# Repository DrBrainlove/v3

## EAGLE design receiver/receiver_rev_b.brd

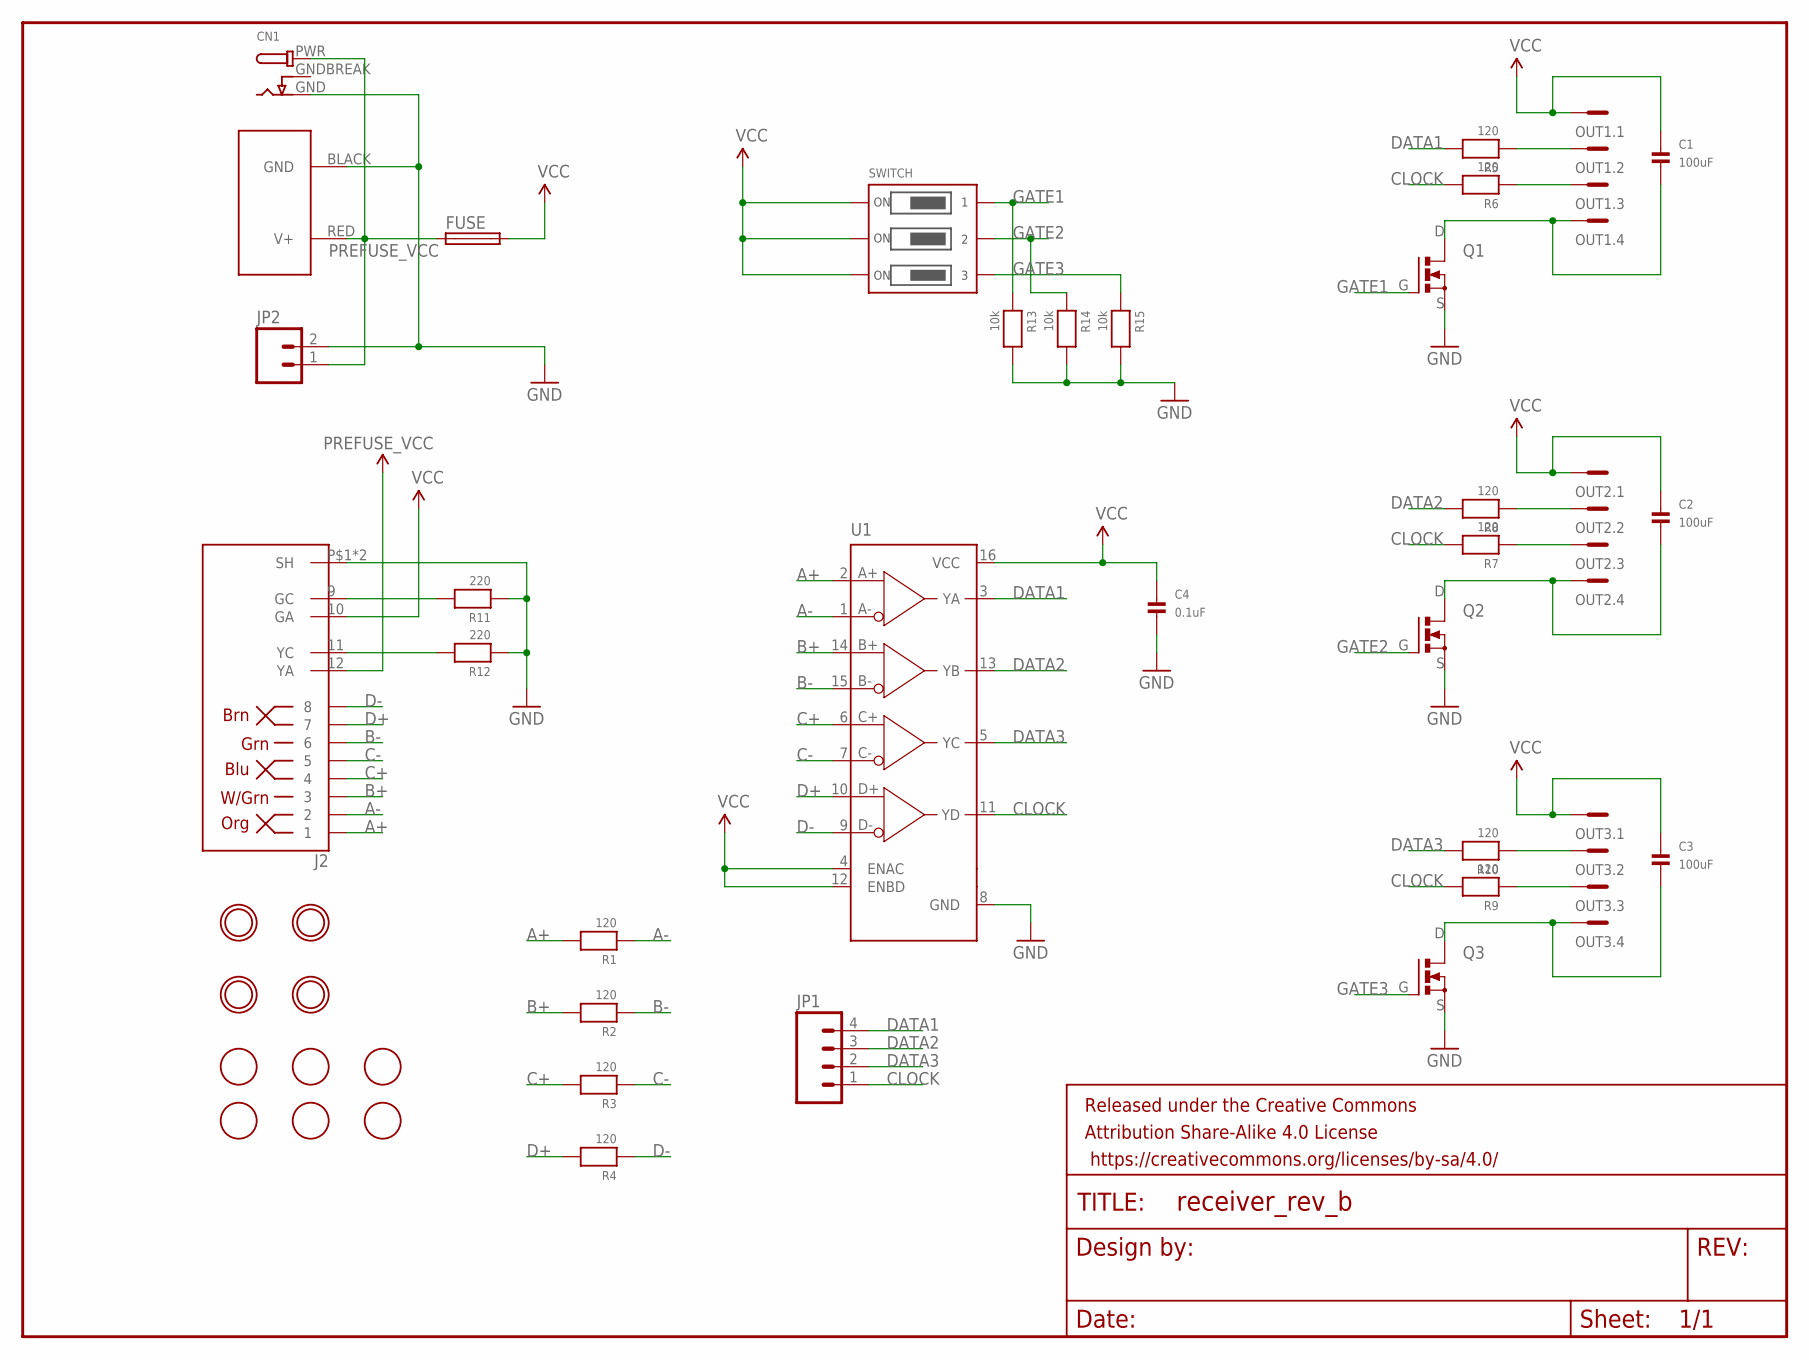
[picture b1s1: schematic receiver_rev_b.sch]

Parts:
C1, C2, C3: 100uF; 1206
C4: 0.1uF; 0603-MINI
CN1: DCBARRELPTH; DCJACK_2MM_PTH
FID1, FID2, FID3, FID4, FID5, FID6: FIDUCIAL; FIDUCIAL_1MM
FRAME1: FRAME-LETTERNO_PACKAGE; DUMMY
FUSE: MINI-FUSE-HOLDER3557; FUSE-HOLDER-3557
J1: POWERPOLE_POWER45A_HORIZONTAL_DRILL; POWERPOLE_PAIR_45A_HORIZ_HOLE
J2: RJHSE-5381; RJHSE-538X
JP1: M04PTH; 1X04
JP2: M02PTH4; 1X02_XTRA_BIG
OUT1, OUT2, OUT3: MC4
Q1, Q2, Q3: DMN1019USN; SC59
R1, R2, R3, R4, R5, R6, R7, R8, R9, R10: 120; 0603-MINI
R11, R12: 220; 0603-MINI
R13, R14, R15: 10k; 0603-MINI
SWITCH: DIP-SWITCH-3PIN194; 194-DIP-SWITCH
U1: MAX3093/94UE; TSSOP16
U$3, U$4, U$5, U$6: MOUNTINGHOLE3.0THIN; MOUNTINGHOLE_3.0_PLATEDTHIN

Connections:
A+: J2.1, R1.2, U1.2 (A+)
A-: J2.2, R1.1, U1.1 (A-)
B+: J2.3, R2.2, U1.14 (B+)
B-: J2.6, R2.1, U1.15 (B-)
C+: J2.4, R3.2, U1.6 (C+)
C-: J2.5, R3.1, U1.7 (C-)
CLOCK: JP1.1, R6.2, R7.2, R9.2, U1.11 (YD)
D+: J2.7, R4.2, U1.10 (D+)
D-: J2.8, R4.1, U1.9 (D-)
DATA1: JP1.4, R5.2, U1.3 (YA)
DATA2: JP1.3, R8.2, U1.13 (YB)
DATA3: JP1.2, R10.2, U1.5 (YC)
GATE1: Q1.G, R13.1, SWITCH.1B
GATE2: Q2.G, R14.1, SWITCH.2B
GATE3: Q3.G, R15.1, SWITCH.3B
GND: C4.2, CN1.GND, J1.BLACK (GND), J2.P$1 (SH), J2.P$2 (SH), JP2.2, Q1.S, Q2.S, Q3.S, R11.1, R12.1, R13.2, R14.2, R15.2, U1.8 (GND)
GNDBREAK: CN1.GNDBREAK
unnamed: OUT1.2, R5.1
unnamed: OUT1.3, R6.1
unnamed: C1.2, OUT1.4, Q1.D
unnamed: OUT2.2, R8.1
unnamed: OUT2.3, R7.1
unnamed: C2.2, OUT2.4, Q2.D
unnamed: OUT3.2, R10.1
unnamed: OUT3.3, R9.1
unnamed: C3.2, OUT3.4, Q3.D
unnamed: J2.9 (GC), R11.2
unnamed: J2.11 (YC), R12.2
PREFUSE_VCC: CN1.PWR, FUSE.A1 (1), FUSE.A2 (1), J1.RED (V+), J2.12 (YA), JP2.1
VCC: C1.1, C2.1, C3.1, C4.1, FUSE.B1 (2), FUSE.B2 (2), J2.10 (GA), OUT1.1, OUT2.1, OUT3.1, SWITCH.1A, SWITCH.2A, SWITCH.3A, U1.4 (ENAC), U1.12 (ENBD), U1.16 (VCC)

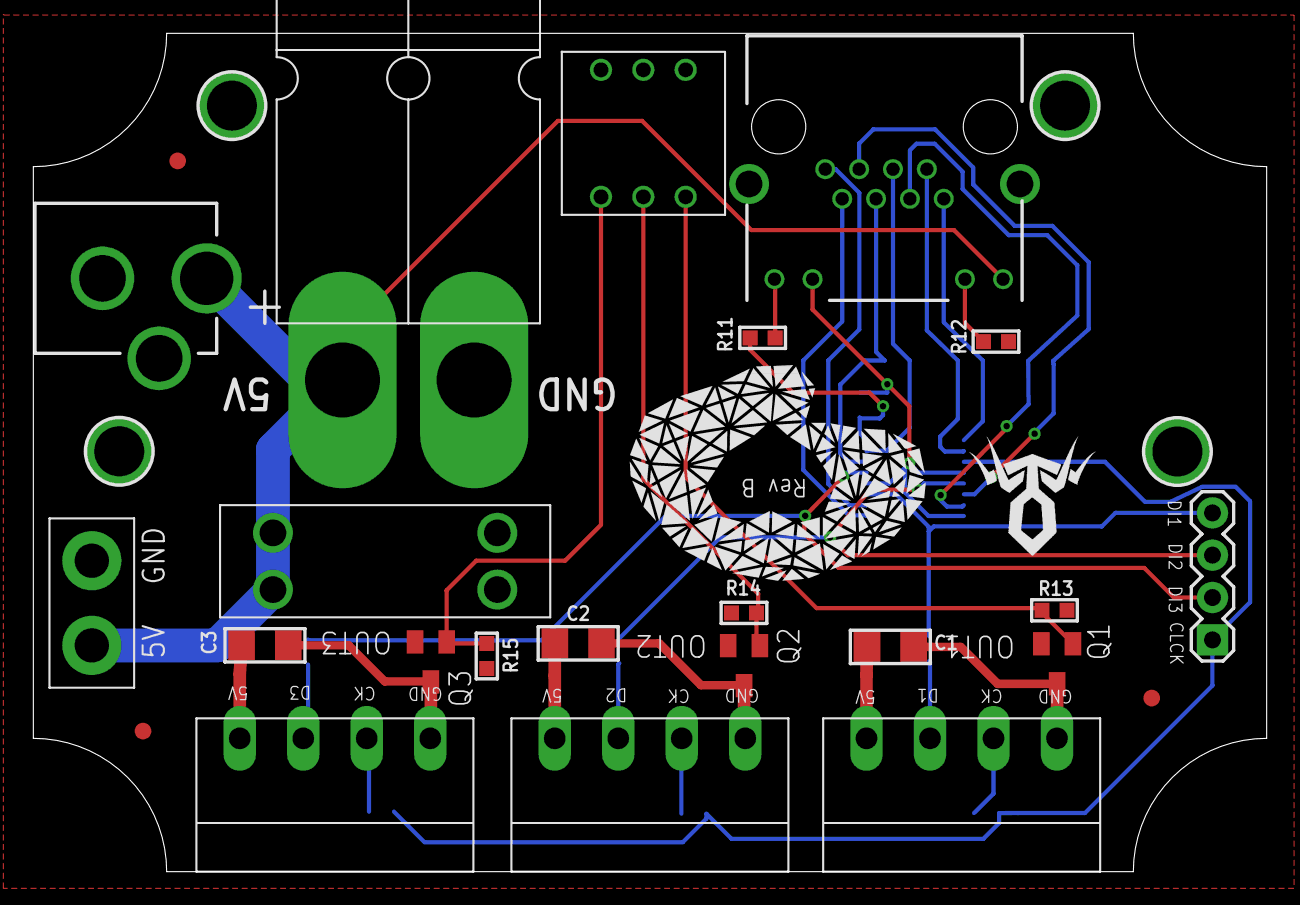
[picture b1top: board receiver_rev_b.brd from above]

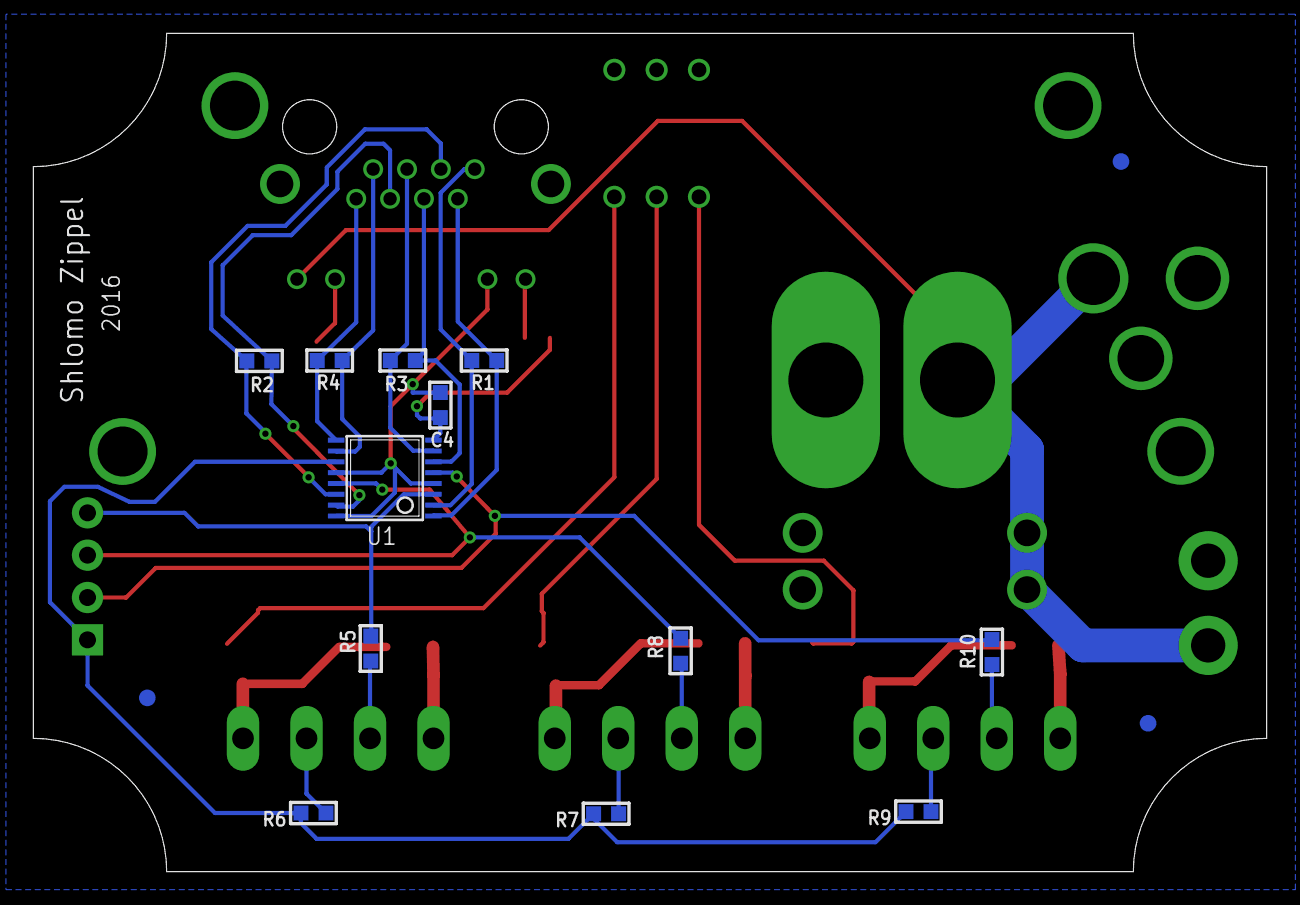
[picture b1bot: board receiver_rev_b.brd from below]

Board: 2 copper layers, 74.0 x 50.3 mm, 45 parts (15 on the bottom side), 29 nets.

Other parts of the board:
U$2: AK-B-FT21

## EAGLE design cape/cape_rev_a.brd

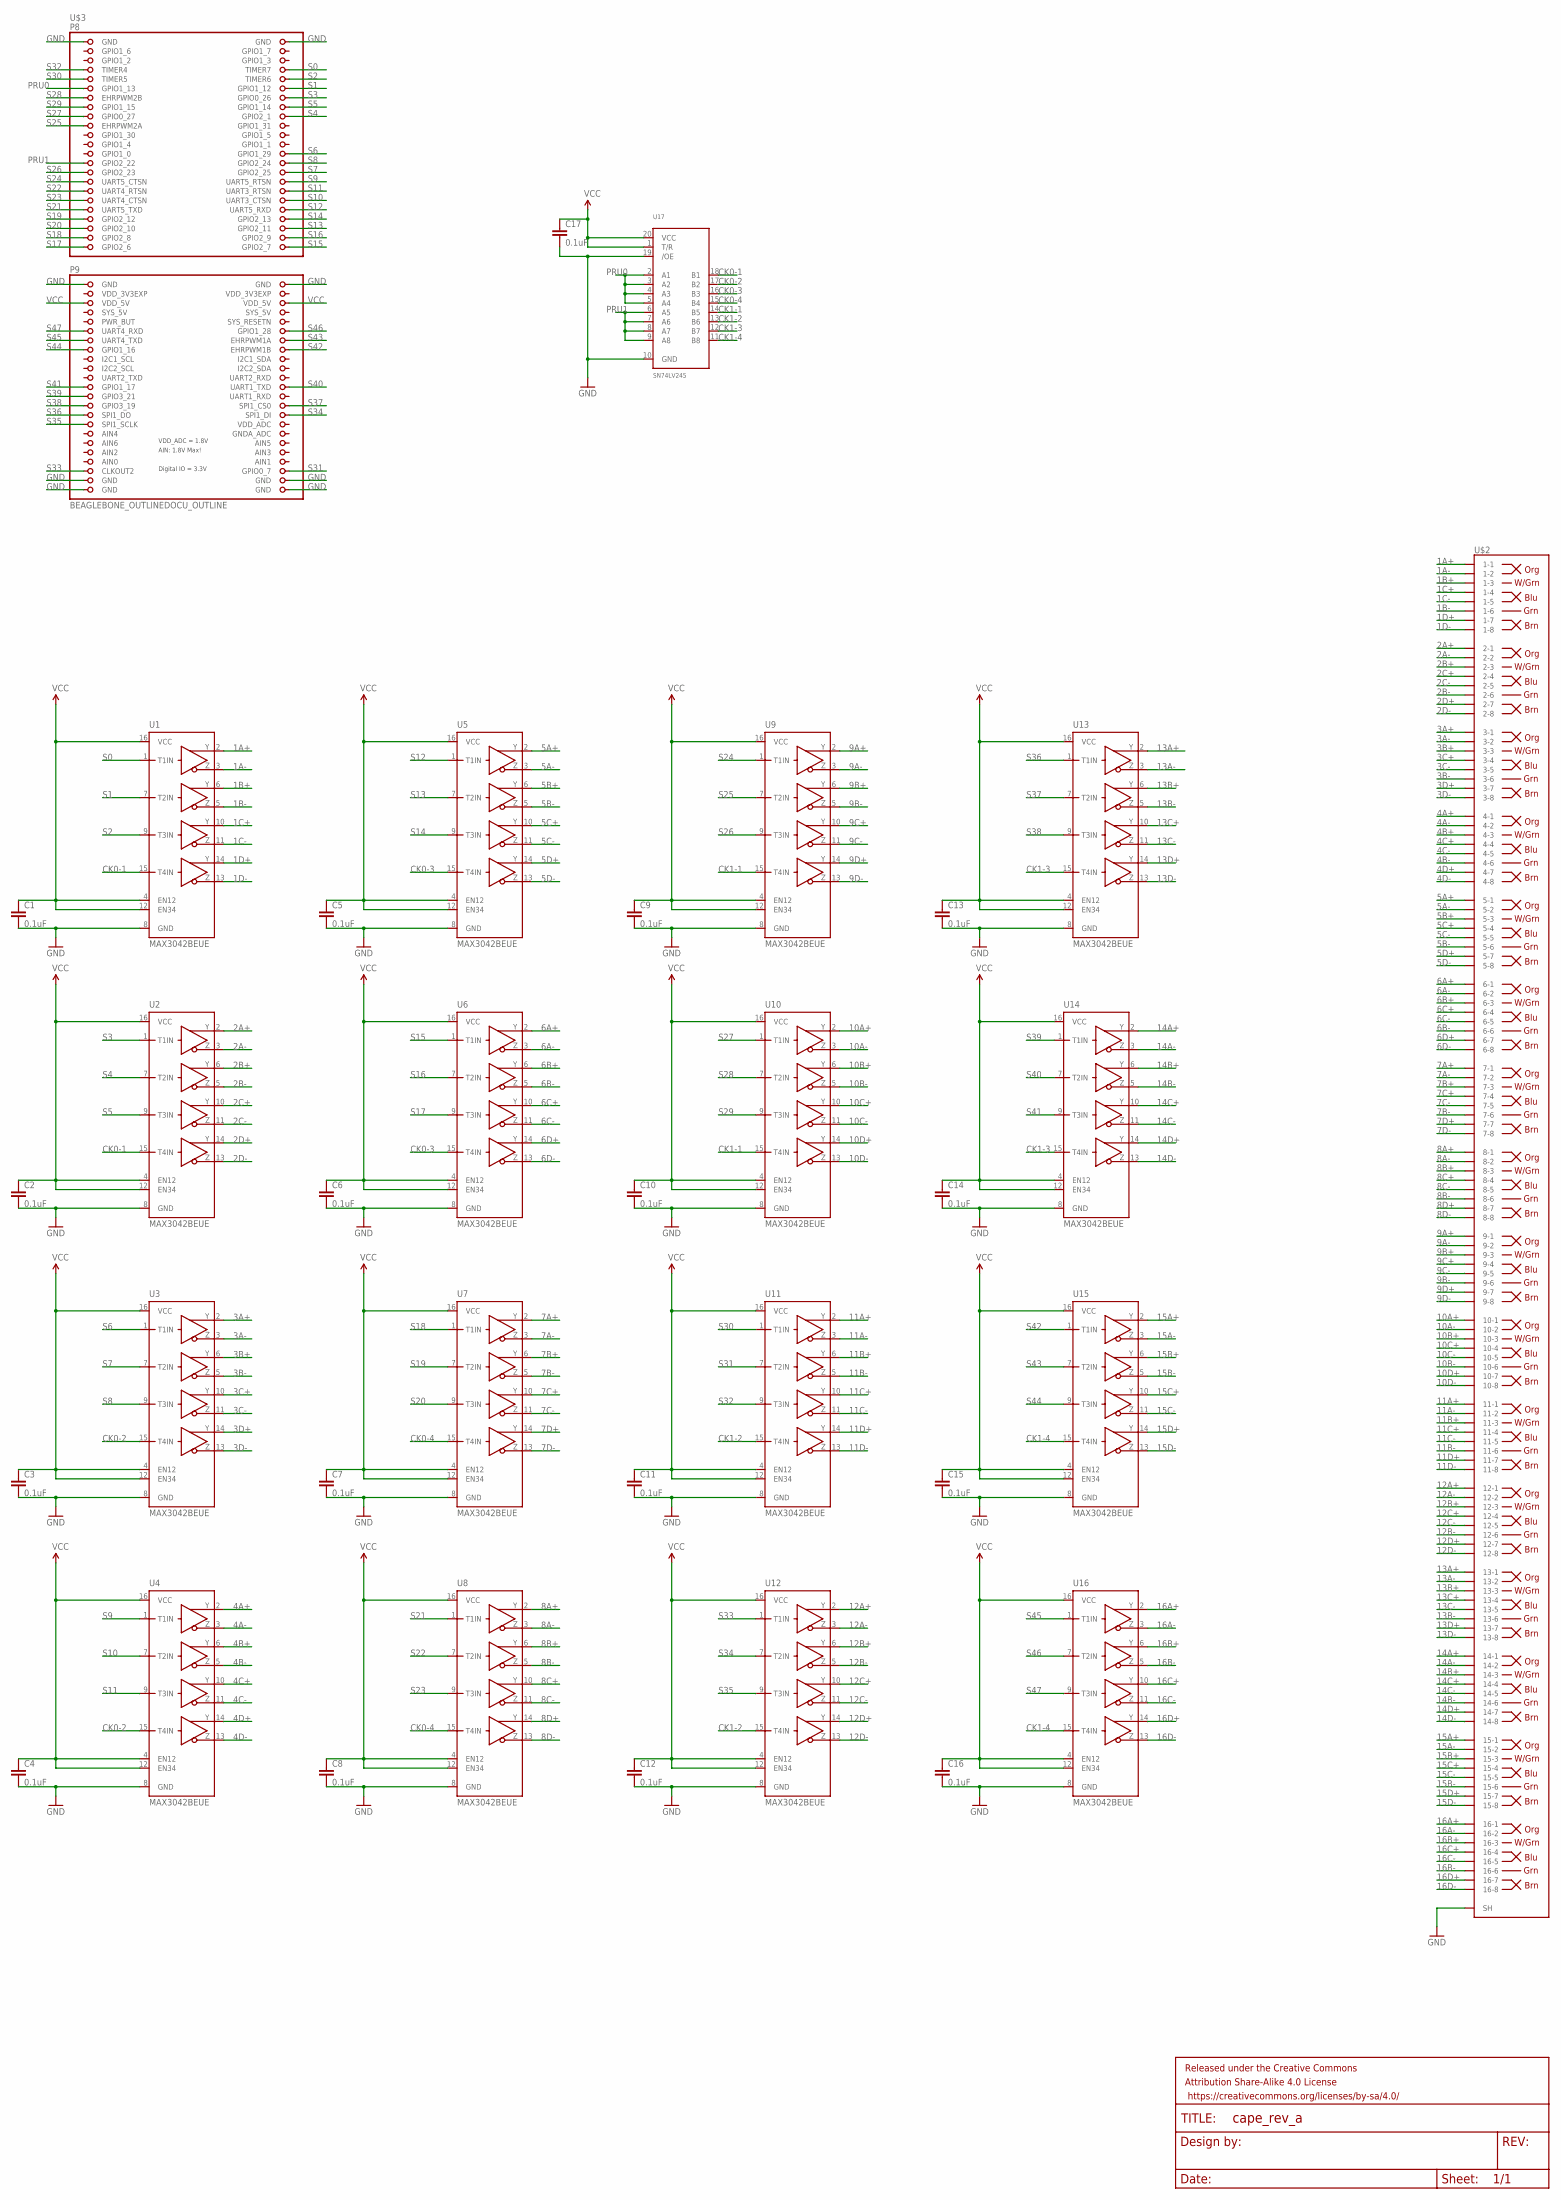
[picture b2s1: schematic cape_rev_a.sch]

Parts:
C1, C2, C3, C4, C5, C6, C7, C8, C9, C10, C11, C12, C13, C14, C15, C16, C17: 0.1uF; 0603-CAP
FRAME1: FRAME-LETTERNO_PACKAGE; DUMMY
U1, U2, U3, U4, U5, U6, U7, U8, U9, U10, U11, U12, U13, U14, U15, U16: MAX3042BEUE; TSSOP16
U17: SN74LV245; TSSOP20
U$2: RJ45-16; 5569264-1
U$3: BEAGLEBONE_OUTLINEDOCU_OUTLINE; BEAGLEBONE_OUTLINE_DOCU

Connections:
1A+: U1.2 (Y1), U$2.P1-1 (1-1)
1A-: U1.3 (Z1), U$2.P1-2 (1-2)
1B+: U1.6 (Y2), U$2.P1-3 (1-3)
1B-: U1.5 (Z2), U$2.P1-6 (1-6)
1C+: U1.10 (Y3), U$2.P1-4 (1-4)
1C-: U1.11 (Z3), U$2.P1-5 (1-5)
1D+: U1.14 (Y4), U$2.P1-7 (1-7)
1D-: U1.13 (Z4), U$2.P1-8 (1-8)
2A+: U2.2 (Y1), U$2.P2-1 (2-1)
2A-: U2.3 (Z1), U$2.P2-2 (2-2)
2B+: U2.6 (Y2), U$2.P2-3 (2-3)
2B-: U2.5 (Z2), U$2.P2-6 (2-6)
2C+: U2.10 (Y3), U$2.P2-4 (2-4)
2C-: U2.11 (Z3), U$2.P2-5 (2-5)
2D+: U2.14 (Y4), U$2.P2-7 (2-7)
2D-: U2.13 (Z4), U$2.P2-8 (2-8)
3A+: U3.2 (Y1), U$2.P3-1 (3-1)
3A-: U3.3 (Z1), U$2.P3-2 (3-2)
3B+: U3.6 (Y2), U$2.P3-3 (3-3)
3B-: U3.5 (Z2), U$2.P3-6 (3-6)
3C+: U3.10 (Y3), U$2.P3-4 (3-4)
3C-: U3.11 (Z3), U$2.P3-5 (3-5)
3D+: U3.14 (Y4), U$2.P3-7 (3-7)
3D-: U3.13 (Z4), U$2.P3-8 (3-8)
4A+: U4.2 (Y1), U$2.P4-1 (4-1)
4A-: U4.3 (Z1), U$2.P4-2 (4-2)
4B+: U4.6 (Y2), U$2.P4-3 (4-3)
4B-: U4.5 (Z2), U$2.P4-6 (4-6)
4C+: U4.10 (Y3), U$2.P4-4 (4-4)
4C-: U4.11 (Z3), U$2.P4-5 (4-5)
4D+: U4.14 (Y4), U$2.P4-7 (4-7)
4D-: U4.13 (Z4), U$2.P4-8 (4-8)
5A+: U5.2 (Y1), U$2.P5-1 (5-1)
5A-: U5.3 (Z1), U$2.P5-2 (5-2)
5B+: U5.6 (Y2), U$2.P5-3 (5-3)
5B-: U5.5 (Z2), U$2.P5-6 (5-6)
5C+: U5.10 (Y3), U$2.P5-4 (5-4)
5C-: U5.11 (Z3), U$2.P5-5 (5-5)
5D+: U5.14 (Y4), U$2.P5-7 (5-7)
5D-: U5.13 (Z4), U$2.P5-8 (5-8)
6A+: U6.2 (Y1), U$2.P6-1 (6-1)
6A-: U6.3 (Z1), U$2.P6-2 (6-2)
6B+: U6.6 (Y2), U$2.P6-3 (6-3)
6B-: U6.5 (Z2), U$2.P6-6 (6-6)
6C+: U6.10 (Y3), U$2.P6-4 (6-4)
6C-: U6.11 (Z3), U$2.P6-5 (6-5)
6D+: U6.14 (Y4), U$2.P6-7 (6-7)
6D-: U6.13 (Z4), U$2.P6-8 (6-8)
7A+: U7.2 (Y1), U$2.P7-1 (7-1)
7A-: U7.3 (Z1), U$2.P7-2 (7-2)
7B+: U7.6 (Y2), U$2.P7-3 (7-3)
7B-: U7.5 (Z2), U$2.P7-6 (7-6)
7C+: U7.10 (Y3), U$2.P7-4 (7-4)
7C-: U7.11 (Z3), U$2.P7-5 (7-5)
7D+: U7.14 (Y4), U$2.P7-7 (7-7)
7D-: U7.13 (Z4), U$2.P7-8 (7-8)
8A+: U8.2 (Y1), U$2.P8-1 (8-1)
8A-: U8.3 (Z1), U$2.P8-2 (8-2)
8B+: U8.6 (Y2), U$2.P8-3 (8-3)
8B-: U8.5 (Z2), U$2.P8-6 (8-6)
8C+: U8.10 (Y3), U$2.P8-4 (8-4)
8C-: U8.11 (Z3), U$2.P8-5 (8-5)
8D+: U8.14 (Y4), U$2.P8-7 (8-7)
8D-: U8.13 (Z4), U$2.P8-8 (8-8)
9A+: U9.2 (Y1), U$2.P9-1 (9-1)
9A-: U9.3 (Z1), U$2.P9-2 (9-2)
9B+: U9.6 (Y2), U$2.P9-3 (9-3)
9B-: U9.5 (Z2), U$2.P9-6 (9-6)
9C+: U9.10 (Y3), U$2.P9-4 (9-4)
9C-: U9.11 (Z3), U$2.P9-5 (9-5)
9D+: U9.14 (Y4), U$2.P9-7 (9-7)
9D-: U9.13 (Z4), U$2.P9-8 (9-8)
10A+: U10.2 (Y1), U$2.P10-1 (10-1)
10A-: U10.3 (Z1), U$2.P10-2 (10-2)
10B+: U10.6 (Y2), U$2.P10-3 (10-3)
10B-: U10.5 (Z2), U$2.P10-6 (10-6)
10C+: U10.10 (Y3), U$2.P10-4 (10-4)
10C-: U10.11 (Z3), U$2.P10-5 (10-5)
10D+: U10.14 (Y4), U$2.P10-7 (10-7)
10D-: U10.13 (Z4), U$2.P10-8 (10-8)
11A+: U11.2 (Y1), U$2.P11-1 (11-1)
11A-: U11.3 (Z1), U$2.P11-2 (11-2)
11B+: U11.6 (Y2), U$2.P11-3 (11-3)
11B-: U11.5 (Z2), U$2.P11-6 (11-6)
11C+: U11.10 (Y3), U$2.P11-4 (11-4)
11C-: U11.11 (Z3), U$2.P11-5 (11-5)
11D+: U11.14 (Y4), U$2.P11-7 (11-7)
11D-: U11.13 (Z4), U$2.P11-8 (11-8)
12A+: U12.2 (Y1), U$2.P12-1 (12-1)
12A-: U12.3 (Z1), U$2.P12-2 (12-2)
12B+: U12.6 (Y2), U$2.P12-3 (12-3)
12B-: U12.5 (Z2), U$2.P12-6 (12-6)
12C+: U12.10 (Y3), U$2.P12-4 (12-4)
12C-: U12.11 (Z3), U$2.P12-5 (12-5)
12D+: U12.14 (Y4), U$2.P12-7 (12-7)
12D-: U12.13 (Z4), U$2.P12-8 (12-8)
13A+: U13.2 (Y1), U$2.P13-1 (13-1)
13A-: U13.3 (Z1), U$2.P13-2 (13-2)
13B+: U13.6 (Y2), U$2.P13-3 (13-3)
13B-: U13.5 (Z2), U$2.P13-6 (13-6)
13C+: U13.10 (Y3), U$2.P13-4 (13-4)
13C-: U13.11 (Z3), U$2.P13-5 (13-5)
13D+: U13.14 (Y4), U$2.P13-7 (13-7)
13D-: U13.13 (Z4), U$2.P13-8 (13-8)
14A+: U14.2 (Y1), U$2.P14-1 (14-1)
14A-: U14.3 (Z1), U$2.P14-2 (14-2)
14B+: U14.6 (Y2), U$2.P14-3 (14-3)
14B-: U14.5 (Z2), U$2.P14-6 (14-6)
14C+: U14.10 (Y3), U$2.P14-4 (14-4)
14C-: U14.11 (Z3), U$2.P14-5 (14-5)
14D+: U14.14 (Y4), U$2.P14-7 (14-7)
14D-: U14.13 (Z4), U$2.P14-8 (14-8)
15A+: U15.2 (Y1), U$2.P15-1 (15-1)
15A-: U15.3 (Z1), U$2.P15-2 (15-2)
15B+: U15.6 (Y2), U$2.P15-3 (15-3)
15B-: U15.5 (Z2), U$2.P15-6 (15-6)
15C+: U15.10 (Y3), U$2.P15-4 (15-4)
15C-: U15.11 (Z3), U$2.P15-5 (15-5)
15D+: U15.14 (Y4), U$2.P15-7 (15-7)
15D-: U15.13 (Z4), U$2.P15-8 (15-8)
16A+: U16.2 (Y1), U$2.P16-1 (16-1)
16A-: U16.3 (Z1), U$2.P16-2 (16-2)
16B+: U16.6 (Y2), U$2.P16-3 (16-3)
16B-: U16.5 (Z2), U$2.P16-6 (16-6)
16C+: U16.10 (Y3), U$2.P16-4 (16-4)
16C-: U16.11 (Z3), U$2.P16-5 (16-5)
16D+: U16.14 (Y4), U$2.P16-7 (16-7)
16D-: U16.13 (Z4), U$2.P16-8 (16-8)
CK0-1: U1.15 (T4IN), U2.15 (T4IN), U17.18 (B1)
CK0-2: U3.15 (T4IN), U4.15 (T4IN), U17.17 (B2)
CK0-3: U5.15 (T4IN), U6.15 (T4IN), U17.16 (B3)
CK0-4: U7.15 (T4IN), U8.15 (T4IN), U17.15 (B4)
CK1-1: U9.15 (T4IN), U10.15 (T4IN), U17.14 (B5)
CK1-2: U11.15 (T4IN), U12.15 (T4IN), U17.13 (B6)
CK1-3: U13.15 (T4IN), U14.15 (T4IN), U17.12 (B7)
CK1-4: U15.15 (T4IN), U16.15 (T4IN), U17.11 (B8)
GND: C1.2, C2.2, C3.2, C4.2, C5.2, C6.2, C7.2, C8.2, C9.2, C10.2, C11.2, C12.2, C13.2, C14.2, C15.2, C16.2, C17.2, U1.8 (GND), U2.8 (GND), U3.8 (GND), U4.8 (GND), U5.8 (GND), U6.8 (GND), U7.8 (GND), U8.8 (GND), U9.8 (GND), U10.8 (GND), U11.8 (GND), U12.8 (GND), U13.8 (GND), U14.8 (GND), U15.8 (GND), U16.8 (GND), U17.10 (GND), U17.19 (/OE), U$2.SH@1 (SH), U$2.SH@2 (SH), U$2.SH@3 (SH), U$2.SH@4 (SH), U$2.SH@5 (SH), U$2.SH@6 (SH), U$3.1 (GND), U$3.2 (GND), U$3.47 (GND), U$3.48 (GND), U$3.89 (GND), U$3.90 (GND), U$3.91 (GND), U$3.92 (GND)
GNDA_ADC: U$3.80 (GNDA_ADC)
PRU0: U17.2 (A1), U17.3 (A2), U17.4 (A3), U17.5 (A4), U$3.11 (GPIO1_13)
PRU1: U17.6 (A5), U17.7 (A6), U17.8 (A7), U17.9 (A8), U$3.27 (GPIO2_22)
S0: U1.1 (T1IN), U$3.8 (TIMER7)
S1: U1.7 (T2IN), U$3.12 (GPIO1_12)
S2: U1.9 (T3IN), U$3.10 (TIMER6)
S3: U2.1 (T1IN), U$3.14 (GPIO0_26)
S4: U2.7 (T2IN), U$3.18 (GPIO2_1)
S5: U2.9 (T3IN), U$3.16 (GPIO1_14)
S6: U3.1 (T1IN), U$3.26 (GPIO1_29)
S7: U3.7 (T2IN), U$3.30 (GPIO2_25)
S8: U3.9 (T3IN), U$3.28 (GPIO2_24)
S9: U4.1 (T1IN), U$3.32 (UART5_RTSN)
S10: U4.7 (T2IN), U$3.36 (UART3_CTSN)
S11: U4.9 (T3IN), U$3.34 (UART3_RTSN)
S12: U5.1 (T1IN), U$3.38 (UART5_RXD)
S13: U5.7 (T2IN), U$3.42 (GPIO2_11)
S14: U5.9 (T3IN), U$3.40 (GPIO2_13)
S15: U6.1 (T1IN), U$3.46 (GPIO2_7)
S16: U6.7 (T2IN), U$3.44 (GPIO2_9)
S17: U6.9 (T3IN), U$3.45 (GPIO2_6)
S18: U7.1 (T1IN), U$3.43 (GPIO2_8)
S19: U7.7 (T2IN), U$3.39 (GPIO2_12)
S20: U7.9 (T3IN), U$3.41 (GPIO2_10)
S21: U8.1 (T1IN), U$3.37 (UART5_TXD)
S22: U8.7 (T2IN), U$3.33 (UART4_RTSN)
S23: U8.9 (T3IN), U$3.35 (UART4_CTSN)
S24: U9.1 (T1IN), U$3.31 (UART5_CTSN)
S25: U9.7 (T2IN), U$3.19 (EHRPWM2A)
S26: U9.9 (T3IN), U$3.29 (GPIO2_23)
S27: U10.1 (T1IN), U$3.17 (GPIO0_27)
S28: U10.7 (T2IN), U$3.13 (EHRPWM2B)
S29: U10.9 (T3IN), U$3.15 (GPIO1_15)
S30: U11.1 (T1IN), U$3.9 (TIMER5)
S31: U11.7 (T2IN), U$3.88 (GPIO0_7)
S32: U11.9 (T3IN), U$3.7 (TIMER4)
S33: U12.1 (T1IN), U$3.87 (CLKOUT2)
S34: U12.7 (T2IN), U$3.76 (SPI1_DI)
S35: U12.9 (T3IN), U$3.77 (SPI1_SCLK)
S36: U13.1 (T1IN), U$3.75 (SPI1_DO)
S37: U13.7 (T2IN), U$3.74 (SPI1_CS0)
S38: U13.9 (T3IN), U$3.73 (GPIO3_19)
S39: U14.1 (T1IN), U$3.71 (GPIO3_21)
S40: U14.7 (T2IN), U$3.70 (UART1_TXD)
S41: U14.9 (T3IN), U$3.69 (GPIO1_17)
S42: U15.1 (T1IN), U$3.62 (EHRPWM1B)
S43: U15.7 (T2IN), U$3.60 (EHRPWM1A)
S44: U15.9 (T3IN), U$3.61 (GPIO1_16)
S45: U16.1 (T1IN), U$3.59 (UART4_TXD)
S46: U16.7 (T2IN), U$3.58 (GPIO1_28)
S47: U16.9 (T3IN), U$3.57 (UART4_RXD)
SYS_5V: U$3.53 (SYS_5V), U$3.54 (SYS_5V)
VCC: C1.1, C2.1, C3.1, C4.1, C5.1, C6.1, C7.1, C8.1, C9.1, C10.1, C11.1, C12.1, C13.1, C14.1, C15.1, C16.1, C17.1, U1.4 (EN12), U1.12 (EN34), U1.16 (VCC), U2.4 (EN12), U2.12 (EN34), U2.16 (VCC), U3.4 (EN12), U3.12 (EN34), U3.16 (VCC), U4.4 (EN12), U4.12 (EN34), U4.16 (VCC), U5.4 (EN12), U5.12 (EN34), U5.16 (VCC), U6.4 (EN12), U6.12 (EN34), U6.16 (VCC), U7.4 (EN12), U7.12 (EN34), U7.16 (VCC), U8.4 (EN12), U8.12 (EN34), U8.16 (VCC), U9.4 (EN12), U9.12 (EN34), U9.16 (VCC), U10.4 (EN12), U10.12 (EN34), U10.16 (VCC), U11.4 (EN12), U11.12 (EN34), U11.16 (VCC), U12.4 (EN12), U12.12 (EN34), U12.16 (VCC), U13.4 (EN12), U13.12 (EN34), U13.16 (VCC), U14.4 (EN12), U14.12 (EN34), U14.16 (VCC), U15.4 (EN12), U15.12 (EN34), U15.16 (VCC), U16.4 (EN12), U16.12 (EN34), U16.16 (VCC), U17.1 (T/R), U17.20 (VCC), U$3.51 (VDD_5V), U$3.52 (VDD_5V)
VDD_3V3EXP: U$3.49 (VDD_3V3EXP), U$3.50 (VDD_3V3EXP)
VDD_ADC: U$3.78 (VDD_ADC)

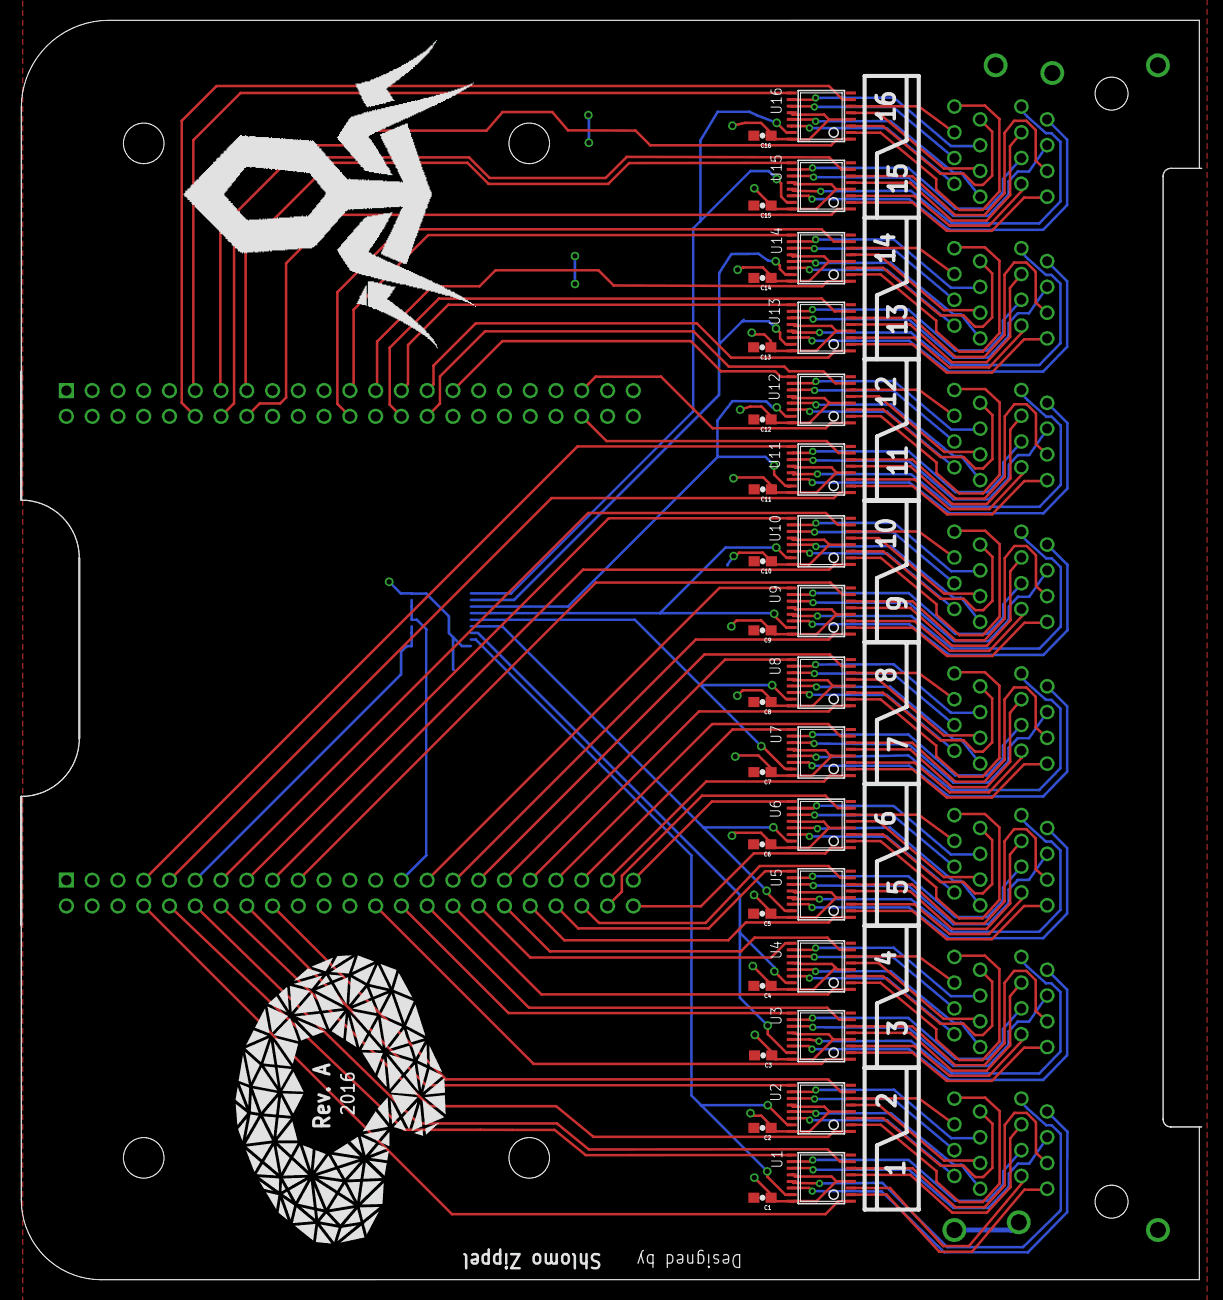
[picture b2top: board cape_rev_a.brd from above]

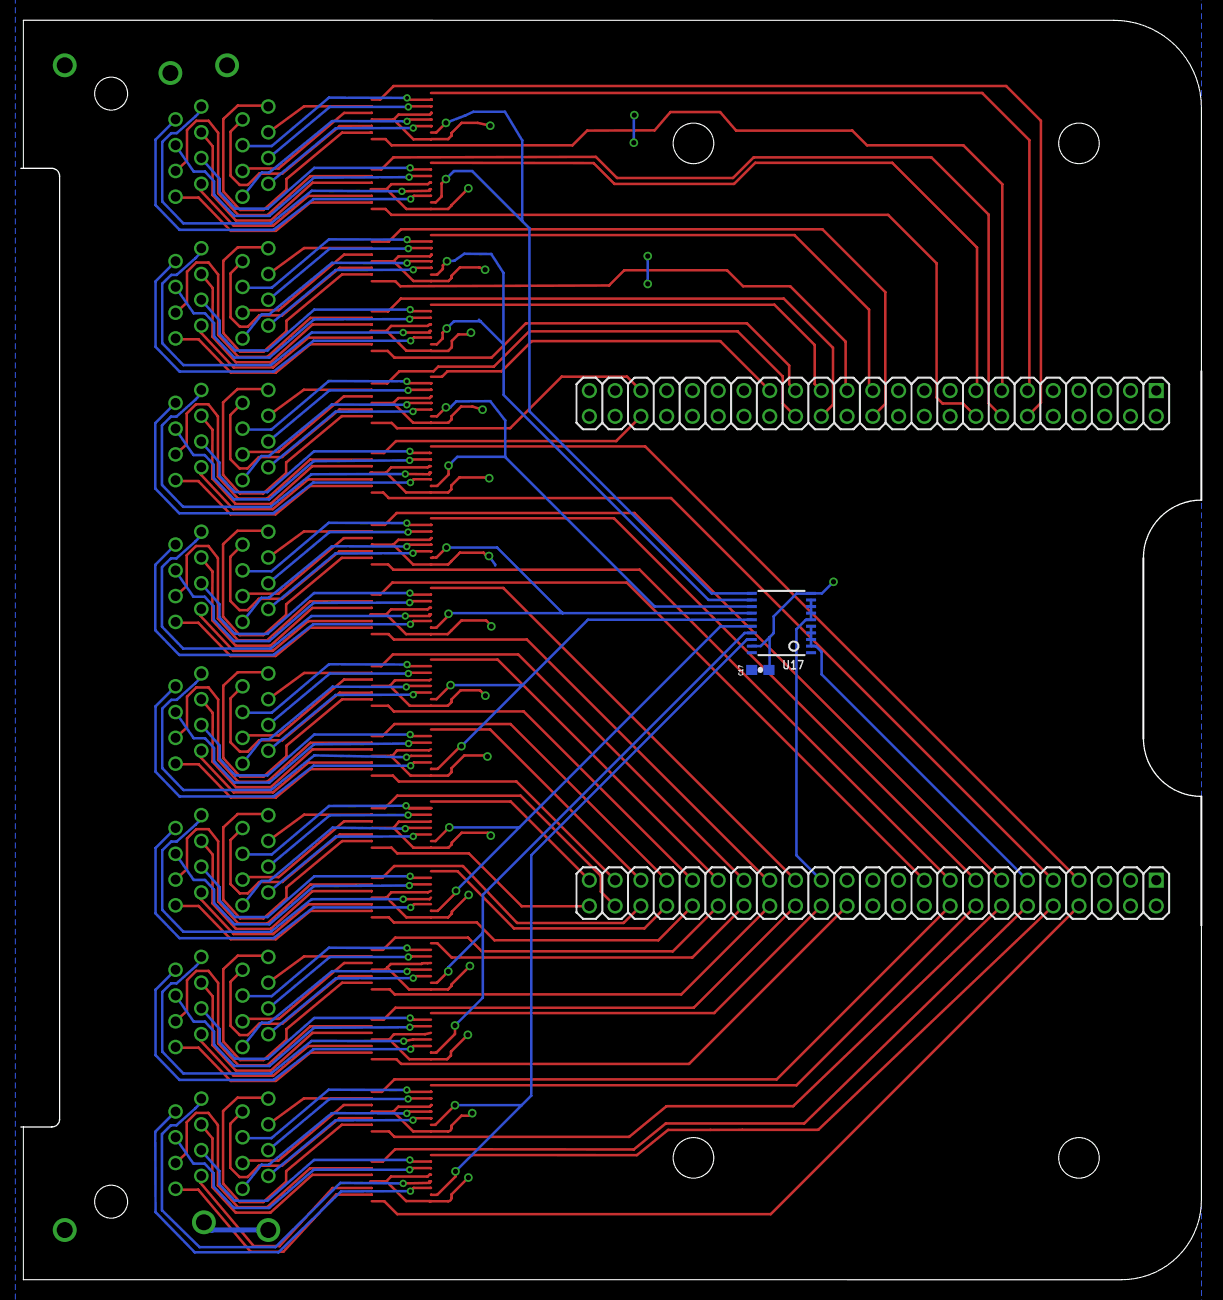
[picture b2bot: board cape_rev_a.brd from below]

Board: 2 copper layers, 116.3 x 123.9 mm, 37 parts (3 on the bottom side), 190 nets.

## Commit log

2016-05-24 Made some progress on layout for cape
2016-05-26 More routing
2016-05-26 cleaned up silkscreen a bit
2016-06-02 Mostly done with the receiver
2016-06-24 Almost done with cape routing
2016-08-07 Cape rev a
2016-08-07 Receiver Rev B
2016-08-07 Minor fix to powerpole pad sizs

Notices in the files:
parts and their libraries:
SparkFun-Aesthetics: Licensing: Creative Commons ShareAlike 4.0 International - https://creativecommons.org/licenses/by-sa/4.0
microbuilder: This work is placed in the public domain, and may be freely used for commercial and non-commercial work with the following conditions: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
